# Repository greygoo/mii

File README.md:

Small tool to chat beween two Wemos D1 mini with RFM69HCW modules.

# Setup

Run ./setup to get the build environment setup. This will update the
submodules, create links and run the setup script from the ESP Makefile
repo to install needed tools.

# Installation

Edit Makefile to adjust serial port, board type and so on. Then connect the
board and run `make upload`.

# Usage

WIP

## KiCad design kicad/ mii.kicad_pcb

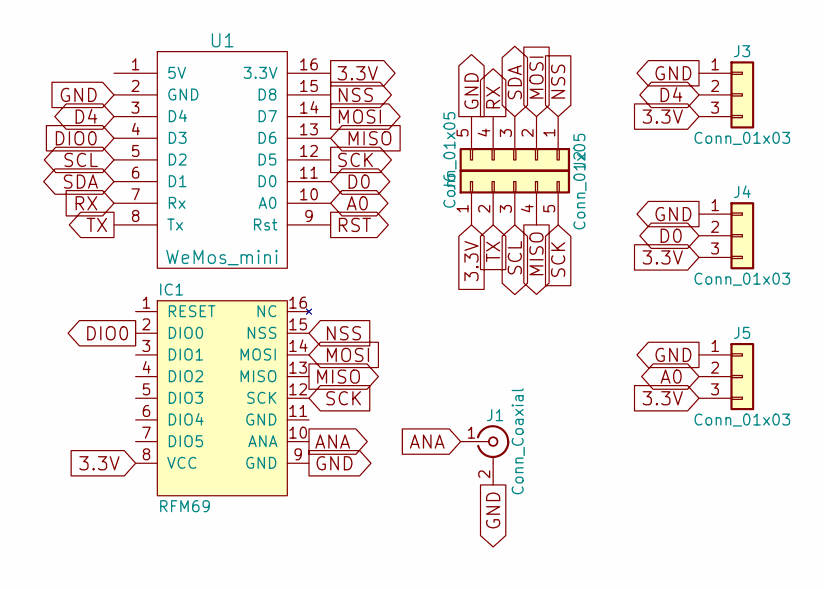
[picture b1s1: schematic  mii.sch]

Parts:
IC1: RFM69; HOPERF-RFM69HW
J1: Conn_Coaxial; SMA_THT_Jack_Straight
J2, J6: Conn_01x05; Pin_Header_Straight_1x05_Pitch2.54mm
J3, J4, J5: Conn_01x03; Molex_KK-6410-03_03x2.54mm_Straight
U1: WeMos_mini; D1_mini_board

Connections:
3.3V: IC1.8 (VCC), J3.3, J4.3, J5.3, J6.1, U1.16 (3.3V)
A0: J5.2, U1.10 (A0)
ANA: IC1.10 (ANA), J1.1 (In)
D0: J4.2, U1.11 (D0)
D4: J3.2, U1.3 (D4)
DIO0: IC1.2 (DIO0), U1.4 (D3)
GND: IC1.9 (GND), J1.2 (Ext), J2.5, J3.1, J4.1, J5.1, U1.2 (GND)
MISO: IC1.13 (MISO), J6.4, U1.13 (D6)
MOSI: IC1.14 (MOSI), J2.2, U1.14 (D7)
NSS: IC1.15 (NSS), J2.1, U1.15 (D8)
RST: U1.9 (Rst)
RX: J2.4, U1.7 (Rx)
SCK: IC1.12 (SCK), J6.5, U1.12 (D5)
SCL: J6.3, U1.5 (D2)
SDA: J2.3, U1.6 (D1)
TX: J6.2, U1.8 (Tx)

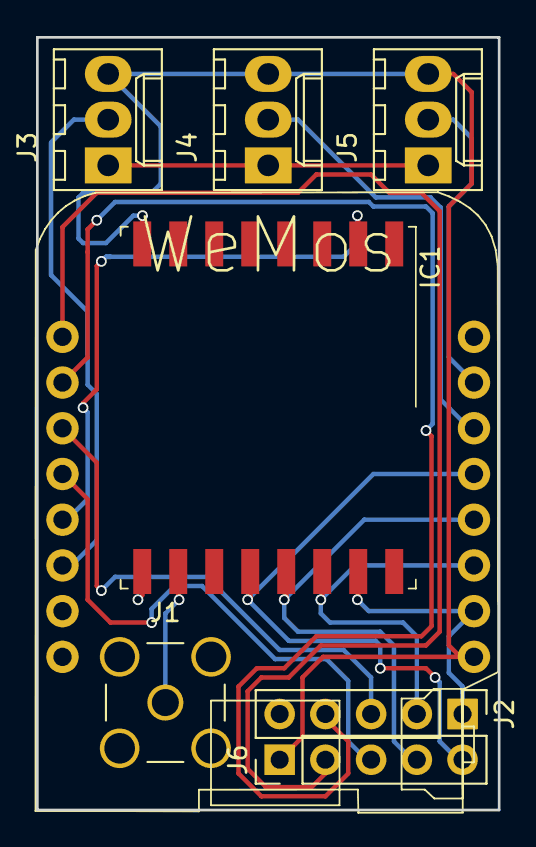
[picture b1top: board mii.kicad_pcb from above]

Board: 2 copper layers, 25.7 x 42.9 mm, 8 parts (0 on the bottom side), 15 nets.

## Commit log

2017-09-23 Devel
2017-09-23 Add files for setting up build environment
2017-09-23 Add serial target to Makefile
2017-09-23 Add README
2017-09-23 Update README with basic description
2017-09-24 Change to https for submodules
2017-09-24 Add missing popd
2017-09-24 Rename rfchat file
2017-09-24 Add codeblocks project file an run screen in xterm
2017-09-24 Add codeblocks layout file
2017-09-24 Add target clean to project
2017-09-24 Another layout change for codeblocks
2017-09-24 Ignore codeblocks layout file
2017-10-07 Add features draft
2017-10-07 rename
2017-10-07 test markdown
2017-10-07 test 2
2017-10-07 fix markdown
2017-10-30 Add testmode to commands, send 0 every 5 seconds
2017-10-30 Enable WLAN AccessPoint and run basic Webserver
2018-10-05 switch to ssl
2018-10-05 Add kicad files
2018-10-05 Add 3d view
2018-10-05 Remove leading space
2018-10-05 Remove text over pads
2018-10-05 Fix boundaries
2018-10-05 Fix Font visibility
2018-10-05 More font fixes
2018-11-11 Change frequency to 433
2018-12-23 Add motionDetect to header
